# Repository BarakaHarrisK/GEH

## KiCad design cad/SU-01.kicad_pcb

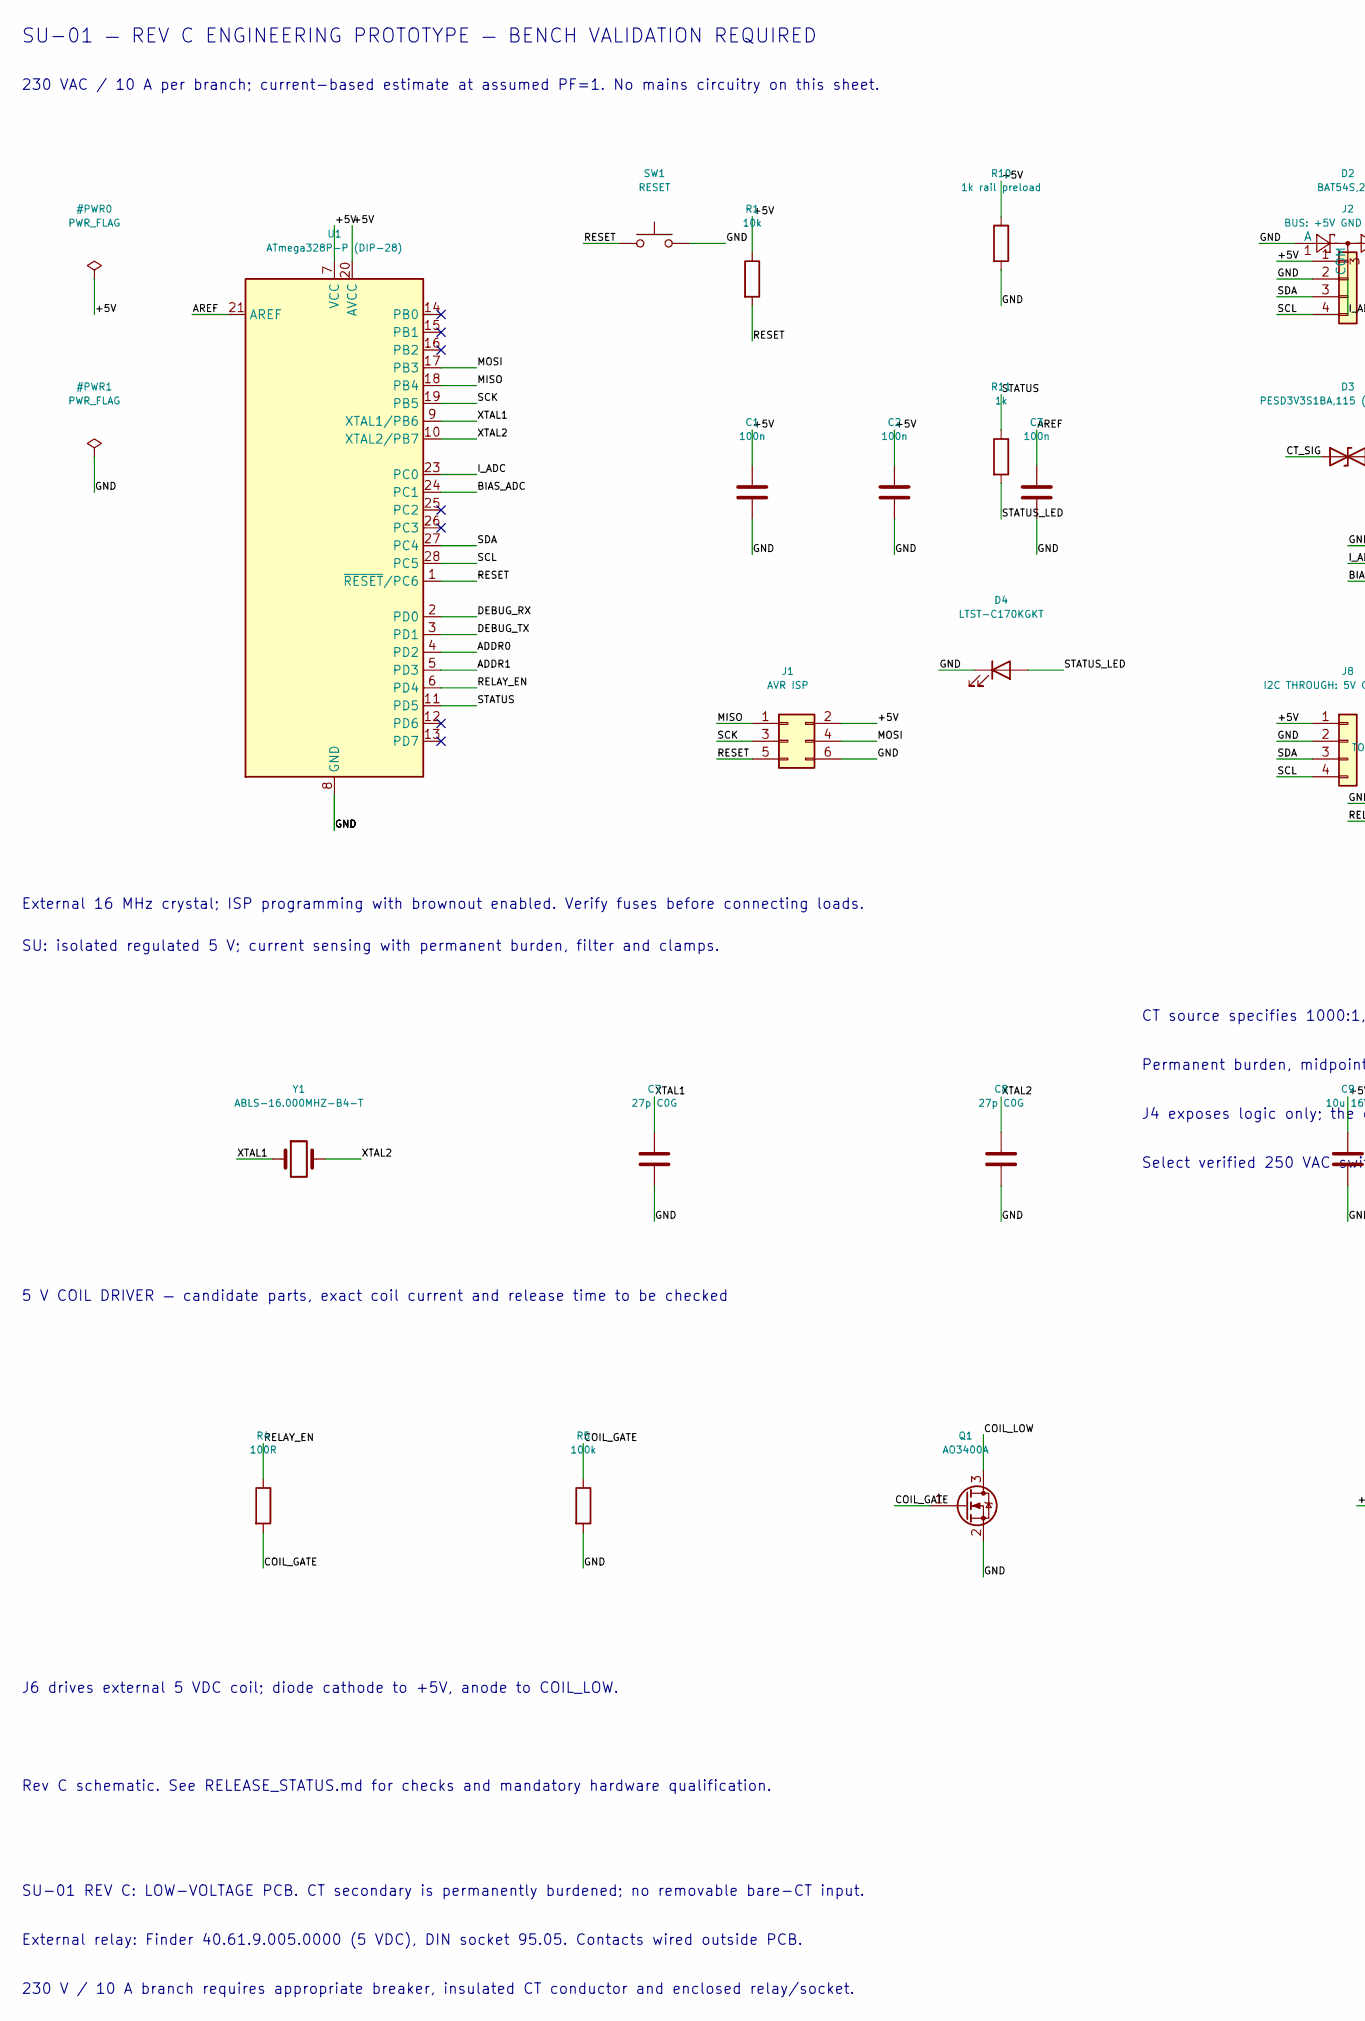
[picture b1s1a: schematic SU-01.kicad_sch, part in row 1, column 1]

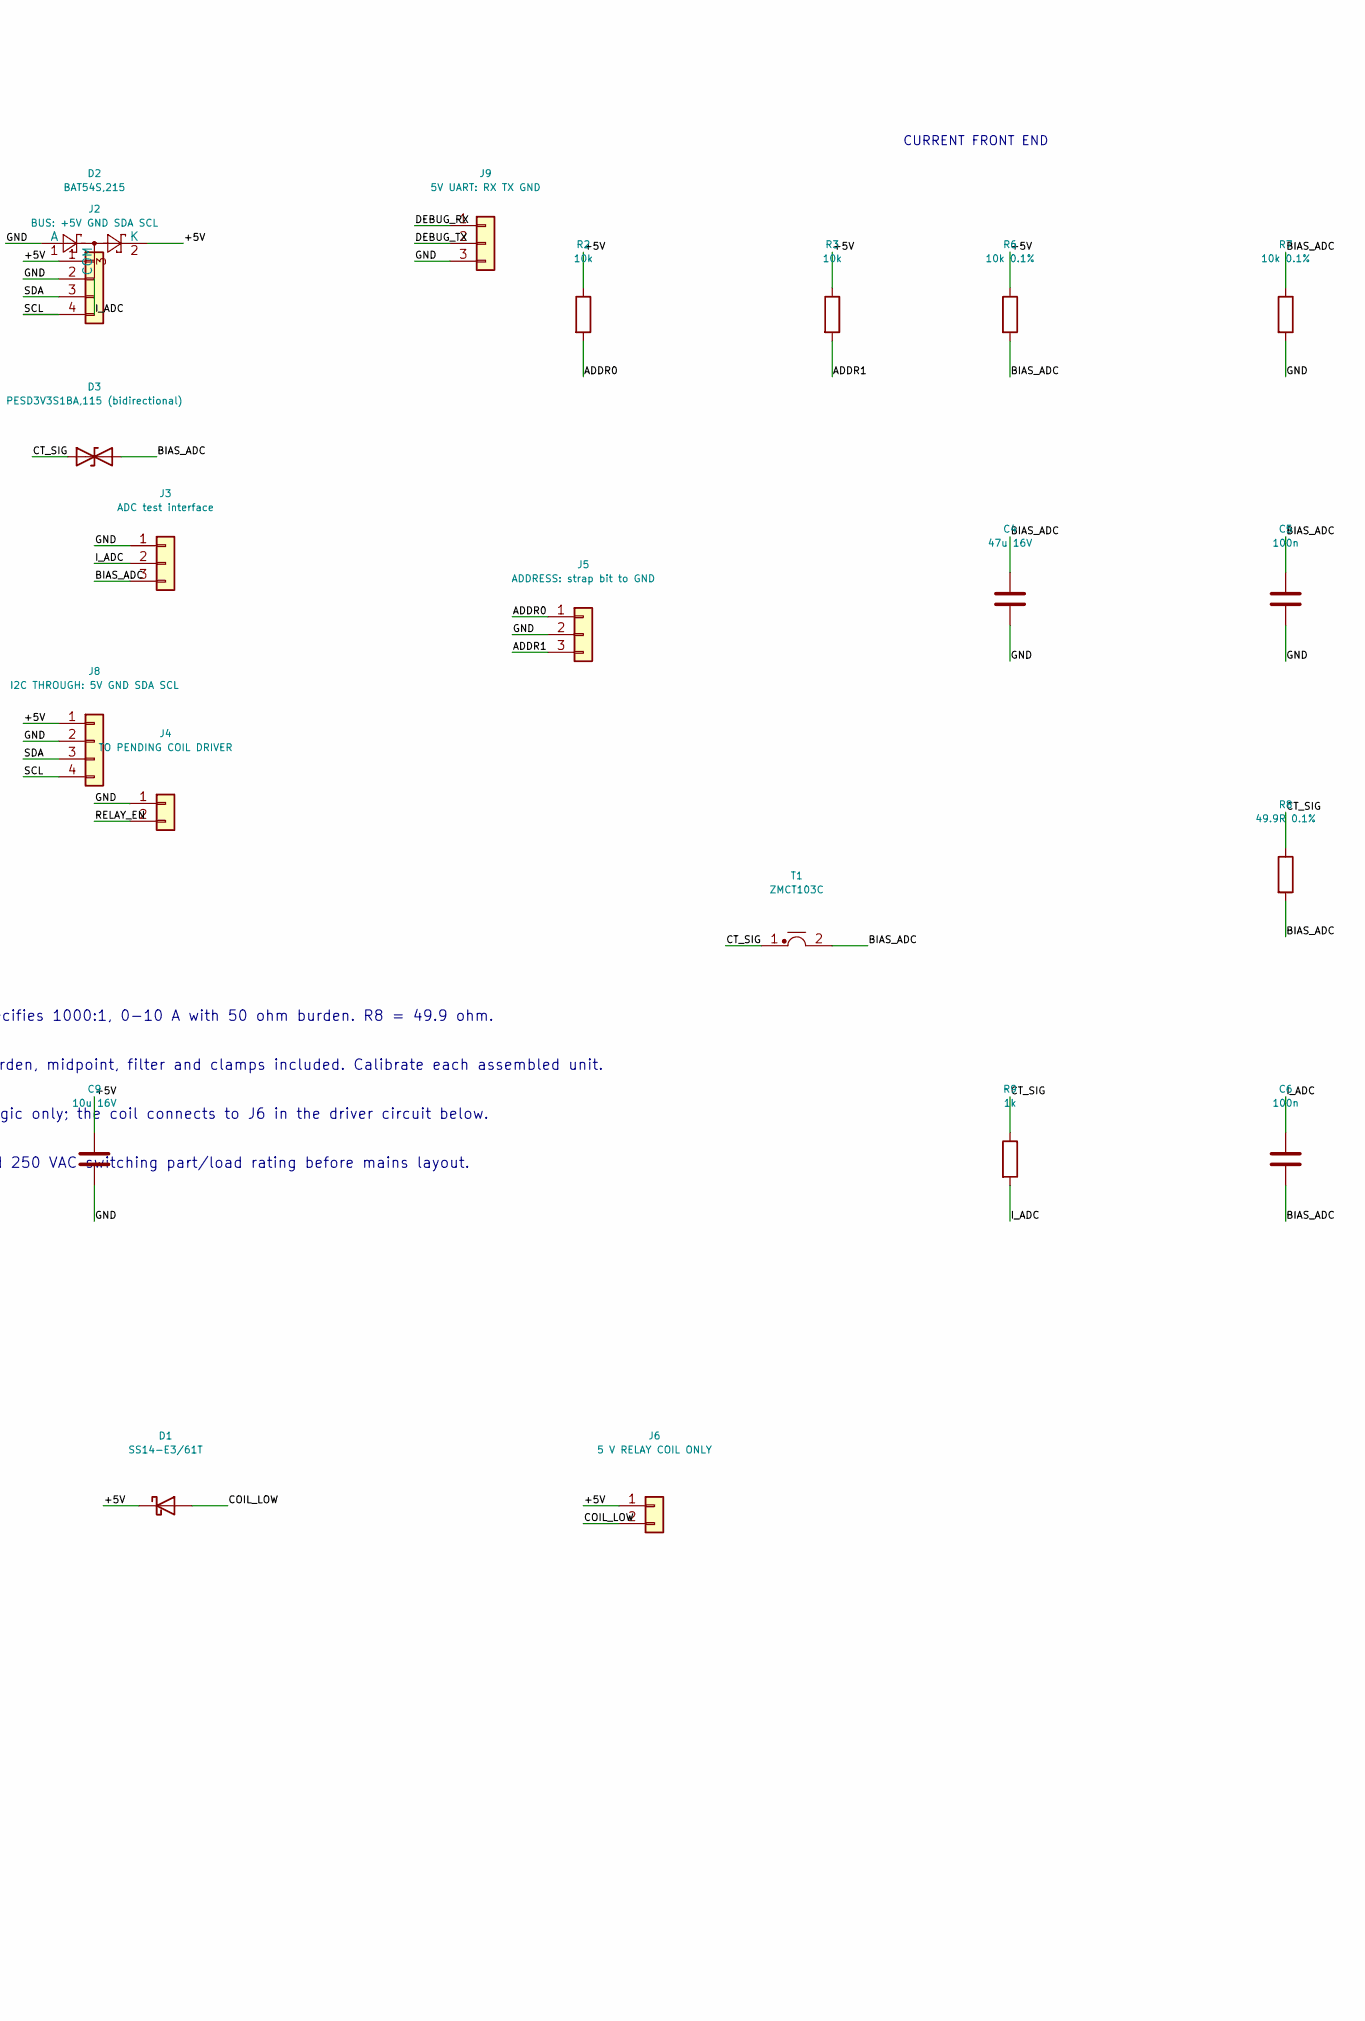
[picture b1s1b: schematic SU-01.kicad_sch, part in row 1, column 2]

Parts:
C1, C2, C3, C5, C6: 100n; C_0805_2012Metric
C4: 47u 16V; CP_Radial_D5.0mm_P2.00mm
C7, C8: 27p C0G; C_0805_2012Metric
C9: 10u 16V; C_1206_3216Metric
D1: SS14-E3/61T; D_SMA
D2: BAT54S,215; SOT-23
D3: PESD3V3S1BA,115 (bidirectional); D_SOD-323
D4: LTST-C170KGKT; LED_0805_2012Metric
J1: AVR ISP; IDC-Header_2x03_P2.54mm_Vertical
J2: BUS: +5V GND SDA SCL; JST_XH_B4B-XH-A_1x04_P2.50mm_Vertical
J3: ADC test interface; PinHeader_1x03_P2.54mm_Vertical
J4: TO PENDING COIL DRIVER; PinHeader_1x02_P2.54mm_Vertical
J5: ADDRESS: strap bit to GND; PinHeader_1x03_P2.54mm_Vertical
J6: 5 V RELAY COIL ONLY; TerminalBlock_Phoenix_MKDS-1,5-2-5.08_1x02_P5.08mm_Horizont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
J8: I2C THROUGH: 5V GND SDA SCL; JST_XH_B4B-XH-A_1x04_P2.50mm_Vertical
J9: 5V UART: RX TX GND; PinHeader_1x03_P2.54mm_Vertical
Q1: AO3400A; SOT-23
R1, R2, R3: 10k; R_0805_2012Metric
R4: 100R; R_0805_2012Metric
R5: 100k; R_0805_2012Metric
R6, R7: 10k 0.1%; R_0805_2012Metric
R8: 49.9R 0.1%; R_0805_2012Metric
R9, R11: 1k; R_0805_2012Metric
R10: 1k rail preload; R_0805_2012Metric
SW1: RESET; SW_PUSH_6mm
T1: ZMCT103C; Transformer_Zeming_ZMCT103C
U1: ATmega328P-P (DIP-28); DIP-28_W7.62mm
Y1: ABLS-16.000MHZ-B4-T; Crystal_HC49-4H_Vertical

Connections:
/ADDR0: J5.1, R2.2, U1.4 (PD2)
/ADDR1: J5.3, R3.2, U1.5 (PD3)
/AREF: C3.1, U1.21 (AREF)
/BIAS_ADC: C4.1, C5.1, C6.2, D3.2 (A2), J3.3, R6.2, R7.1, R8.2, T1.2, U1.24 (PC1)
/COIL_GATE: Q1.1 (G), R4.2, R5.1
/COIL_LOW: D1.2 (A), J6.2, Q1.3 (D)
/CT_SIG: D3.1 (A1), R8.1, R9.1, T1.1
/DEBUG_RX: J9.1, U1.2 (PD0)
/DEBUG_TX: J9.2, U1.3 (PD1)
/I_ADC: C6.1, D2.3 (COM), J3.2, R9.2, U1.23 (PC0)
/MISO: J1.1, U1.18 (PB4)
/MOSI: J1.4, U1.17 (PB3)
/RELAY_EN: J4.2, R4.1, U1.6 (PD4)
/RESET: J1.5, R1.2, SW1.1, U1.1 (~RESET/PC6)
/SCK: J1.3, U1.19 (PB5)
/SCL: J2.4, J8.4, U1.28 (PC5)
/SDA: J2.3, J8.3, U1.27 (PC4)
/STATUS: R11.1, U1.11 (PD5)
/STATUS_LED: D4.2 (A), R11.2
/XTAL1: C7.1, U1.9 (XTAL1/PB6), Y1.1
/XTAL2: C8.1, U1.10 (XTAL2/PB7), Y1.2

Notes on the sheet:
SU-01 — REV C ENGINEERING PROTOTYPE — BENCH VALIDATION REQUIRED
230 VAC / 10 A per branch; current-based estimate at assumed PF=1. No mains circuitry on this sheet.
External 16 MHz crystal; ISP programming with brownout enabled. Verify fuses before connecting loads.
SU: isolated regulated 5 V; current sensing with permanent burden, filter and clamps.
CT source specifies 1000:1, 0-10 A with 50 ohm burden. R8 = 49.9 ohm.
Permanent burden, midpoint, filter and clamps included. Calibrate each assembled unit.
J4 exposes logic only; the coil connects to J6 in the driver circuit below.
Select verified 250 VAC switching part/load rating before mains layout.
CURRENT FRONT END
5 V COIL DRIVER — candidate parts, exact coil current and release time to be checked
J6 drives external 5 VDC coil; diode cathode to +5V, anode to COIL_LOW.
SU-01 REV C: LOW-VOLTAGE PCB. CT secondary is permanently burdened; no removable bare-CT input.
External relay: Finder 40.61.9.005.0000 (5 VDC), DIN socket 95.05. Contacts wired outside PCB.
230 V / 10 A branch requires appropriate breaker, insulated CT conductor and enclosed relay/socket.
Rev C schematic. See RELEASE_STATUS.md for checks and mandatory hardware qualification.

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
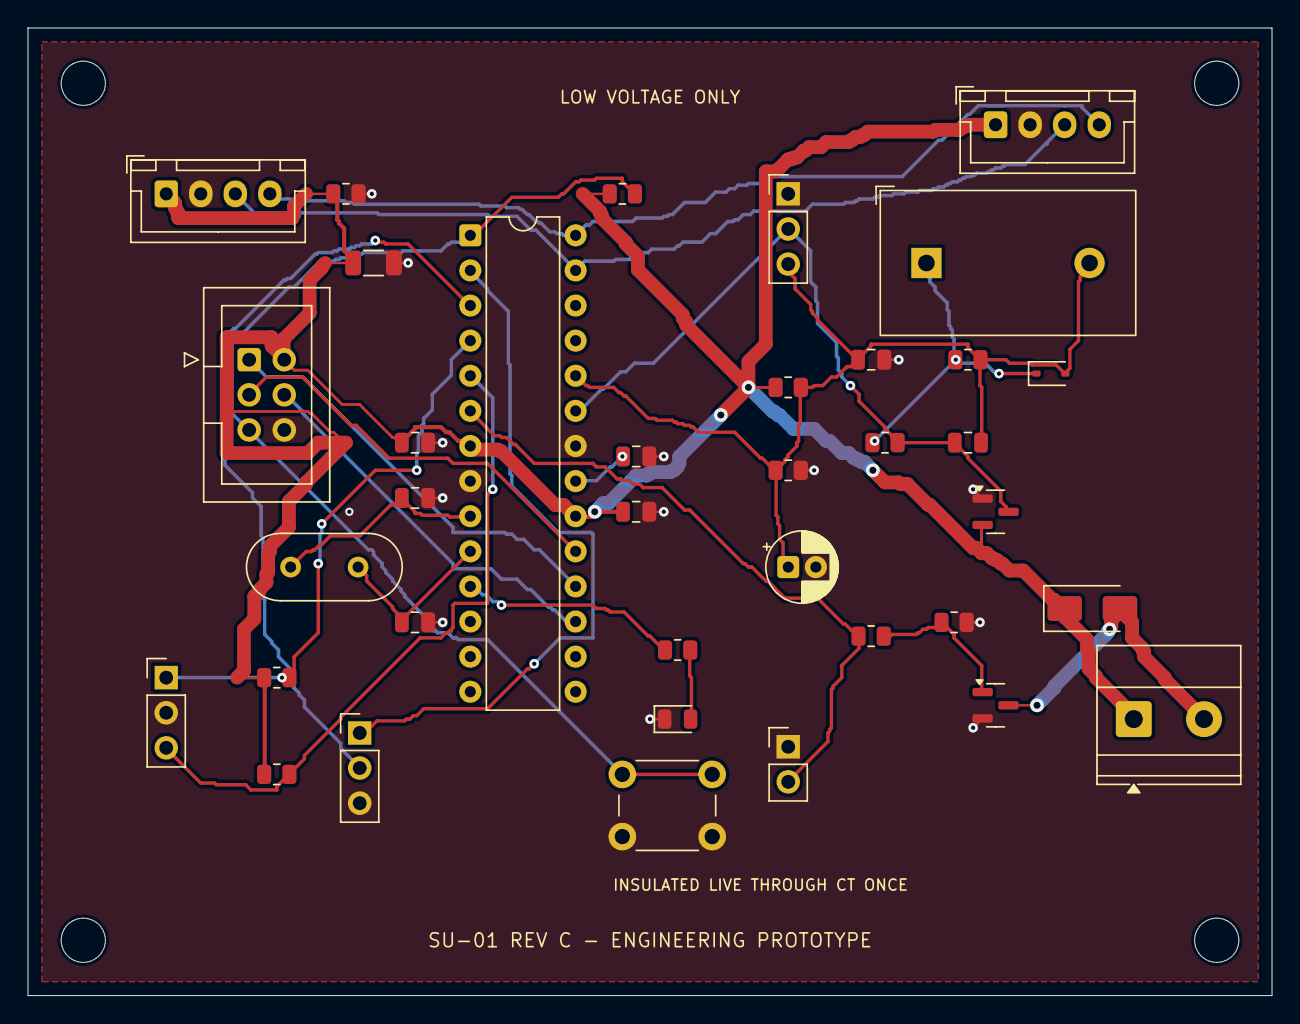
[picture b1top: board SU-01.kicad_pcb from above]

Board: 2 copper layers, 90.0 x 70.0 mm, 41 parts (0 on the bottom side), 23 nets.

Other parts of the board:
H1, H2, H3, H4: MountingHole_3.2mm_M3

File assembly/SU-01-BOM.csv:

Board,References,Qty per board,Qty for system,Value,Manufacturer part number,Footprint,Procurement requirements
SU-01,"C1,C2,C3,C5,C6",5,20,100n,,Capacitor_SMD:C_0805_2012Metric,100n; voltage >=stated or 25 V if unstated; X7R unless C0G specified; verify effective capacitance under DC bias; match listed case size.
SU-01,C4,1,4,47u 16V,,Capacitor_THT:CP_Radial_D5.0mm_P2.00mm,"47u 16V; radial, 5 mm diameter, 2.0 mm lead pitch; >=105 C, low ESR."
SU-01,"C7,C8",2,8,27p C0G,,Capacitor_SMD:C_0805_2012Metric,27p C0G; voltage >=stated or 25 V if unstated; X7R unless C0G specified; verify effective capacitance under DC bias; match listed case size.
SU-01,C9,1,4,10u 16V,,Capacitor_SMD:C_1206_3216Metric,10u 16V; voltage >=stated or 25 V if unstated; X7R unless C0G specified; verify effective capacitance under DC bias; match listed case size.
SU-01,D1,1,4,SS14-E3/61T,SS14-E3/61T,Diode_SMD:D_SMA,Use exact MPN and package; no unreviewed substitutions
SU-01,D2,1,4,"BAT54S,215","BAT54S,215",Package_TO_SOT_SMD:SOT-23,Use exact MPN and package; no unreviewed substitutions
SU-01,D3,1,4,"PESD3V3S1BA,115 (bidirectional)","PESD3V3S1BA,115",Diode_SMD:D_SOD-323,Use exact MPN and package; no unreviewed substitutions
SU-01,D4,1,4,LTST-C170KGKT,LTST-C170KGKT,LED_SMD:LED_0805_2012Metric,Use exact MPN and package; no unreviewed substitutions
SU-01,J1,1,4,AVR ISP,,Connector_IDC:IDC-Header_2x03_P2.54mm_Vertical,AVR ISP; standard 2.54 mm header matching listed footprint; pin numbers in connector schedule
SU-01,J2,1,4,BUS: +5V GND SDA SCL,B4B-XH-A(LF)(SN),Connector_JST:JST_XH_B4B-XH-A_1x04_P2.50mm_Vertical,JST XH 4-pin; mating XHP-4 with SXH-001T-P0.6 crimp contacts
SU-01,J3,1,4,ADC test interface,,Connector_PinHeader_2.54mm:PinHeader_1x03_P2.54mm_Vertical,ADC test interface; standard 2.54 mm header matching listed footprint; pin numbers in connector schedule
SU-01,J4,1,4,TO PENDING COIL DRIVER,,Connector_PinHeader_2.54mm:PinHeader_1x02_P2.54mm_Vertical,TO PENDING COIL DRIVER; standard 2.54 mm header matching listed footprint; pin numbers in connector schedule
SU-01,J5,1,4,ADDRESS: strap bit to GND,,Connector_PinHeader_2.54mm:PinHeader_1x03_P2.54mm_Vertical,ADDRESS: strap bit to GND; standard 2.54 mm header matching listed footprint; pin numbers in connector schedule
SU-01,J6,1,4,5 V RELAY COIL ONLY,Phoenix Contact 1715721,"TerminalBlock_Phoenix:TerminalBlock_Phoenix_MKDS-1,5-2-5.08_1x02_P5.08mm_Horizontal",MKDS 1.5/2-5.08 coil connector; verify exact terminal outline against selected drawing
SU-01,J8,1,4,I2C THROUGH: 5V GND SDA SCL,B4B-XH-A(LF)(SN),Connector_JST:JST_XH_B4B-XH-A_1x04_P2.50mm_Vertical,JST XH 4-pin; mating XHP-4 with SXH-001T-P0.6 crimp contacts
SU-01,J9,1,4,5V UART: RX TX GND,,Connector_PinHeader_2.54mm:PinHeader_1x03_P2.54mm_Vertical,5V UART: RX TX GND; standard 2.54 mm header matching listed footprint; pin numbers in connector schedule
SU-01,Q1,1,4,AO3400A,AO3400A,Package_TO_SOT_SMD:SOT-23,Use exact MPN and package; no unreviewed substitutions
SU-01,"R1,R2,R3",3,12,10k,,Resistor_SMD:R_0805_2012Metric,10k; 0805 >=0.125 W unless footprint is 2512 (>=1 W); stated 0.1% values require precision thin-film; other resistors 1%.
SU-01,R10,1,4,1k rail preload,,Resistor_SMD:R_0805_2012Metric,1k rail preload; 0805 >=0.125 W unless footprint is 2512 (>=1 W); stated 0.1% values require precision thin-film; other resistors 1%.
SU-01,R4,1,4,100R,,Resistor_SMD:R_0805_2012Metric,100R; 0805 >=0.125 W unless footprint is 2512 (>=1 W); stated 0.1% values require precision thin-film; other resistors 1%.
SU-01,R5,1,4,100k,,Resistor_SMD:R_0805_2012Metric,100k; 0805 >=0.125 W unless footprint is 2512 (>=1 W); stated 0.1% values require precision thin-film; other resistors 1%.
SU-01,"R6,R7",2,8,10k 0.1%,,Resistor_SMD:R_0805_2012Metric,10k 0.1%; 0805 >=0.125 W unless footprint is 2512 (>=1 W); stated 0.1% values require precision thin-film; other resistors 1%.
SU-01,R8,1,4,49.9R 0.1%,,Resistor_SMD:R_0805_2012Metric,49.9R 0.1%; 0805 >=0.125 W unless footprint is 2512 (>=1 W); stated 0.1% values require precision thin-film; other resistors 1%.
SU-01,"R9,R11",2,8,1k,,Resistor_SMD:R_0805_2012Metric,1k; 0805 >=0.125 W unless footprint is 2512 (>=1 W); stated 0.1% values require precision thin-film; other resistors 1%.
SU-01,SW1,1,4,RESET,,Button_Switch_THT:SW_PUSH_6mm,"6 x 6 mm through-hole normally-open tactile switch, pin layout matches footprint"
SU-01,T1,1,4,ZMCT103C,ZMCT103C,Transformer_THT:Transformer_Zeming_ZMCT103C,Use exact MPN and package; no unreviewed substitutions
SU-01,U1,1,4,ATmega328P-P (DIP-28),ATMEGA328P-PU,Package_DIP:DIP-28_W7.62mm,Use exact MPN and package; no unreviewed substitutions
SU-01,Y1,1,4,ABLS-16.000MHZ-B4-T,ABLS-16.000MHZ-B4-T,Crystal:Crystal_HC49-4H_Vertical,Use exact MPN and package; no unreviewed substitutions

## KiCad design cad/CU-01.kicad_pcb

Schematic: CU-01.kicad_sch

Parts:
BT1: 18650 3.7V 2600mAh cell 1; BatteryHolder_Keystone_1042_1x18650
BT2: 18650 3.7V 2600mAh cell 2; BatteryHolder_Keystone_1042_1x18650
C1, C2, C3, C6, C7, C8, C9, C15, C21, C22, C33, C38, C39, C42, C43: 100n; C_0805_2012Metric
C4, C5: 1u; C_0805_2012Metric
C10, C16: 10u 25V X7R; C_1210_3225Metric
C12, C17, C20, C30, C31, C32: 100n 25V; C_0805_2012Metric
C13, C14, C19: 22u 25V X7R; C_1210_3225Metric
C18: 3.3n; C_0805_2012Metric
C23: 47n 25V; C_0805_2012Metric
C24, C25: 1u 25V; C_0805_2012Metric
C26: 1u 10V; C_0805_2012Metric
C27, C28, C29: 10u 25V; C_1210_3225Metric
C34, C35: 100n 16V; C_0805_2012Metric
C36, C37: 100n 10V; C_0805_2012Metric
C40, C41: 27p C0G; C_0805_2012Metric
D2, D3: BAT46W-E3-08; D_SOD-123
D4: LTST-C170KGKT; LED_0805_2012Metric
D5: LTST-C170KRKT; LED_0805_2012Metric
D6: BZT52C12-E3-08; D_SOD-123
F1, F2: 0451003.MRL 3A 125V; Fuse_Littelfuse-NANO2-451_453
J1: AVR ISP; IDC-Header_2x03_P2.54mm_Vertical
J2: BUS: mains-only 5 V, GND, SDA, SCL; JST_XH_B4B-XH-A_1x04_P2.50mm_Vertical
J3: 4x4 passive keypad; PinHeader_1x08_P2.54mm_Vertical
J4: LCD1602 5V 20mA BACKLIGHT; PinHeader_1x16_P2.54mm_Vertical
J5: GSM INTERFACE TO PENDING CIRCUIT; PinHeader_1x04_P2.54mm_Vertical
J6: SIM800L HARNESS (not module footprint); JST_XH_B5B-XH-A_1x05_P2.50mm_Vertical
J7: ISOLATED 12 V INPUT; TerminalBlock_Phoenix_MKDS-3-2-5.08_1x02_P5.08mm_Horizontal
J9: CHARGE INHIBIT: short ISET to GND; PinHeader_1x02_P2.54mm_Vertical
J10: CELL TEMPERATURE SENSOR; JST_XH_B2B-XH-A_1x02_P2.50mm_Vertical
L2: XAL6030-222MEB 2.2uH; L_Coilcraft_XAL6030-XXX
L3: XAL6030-332MEB 3.3uH; L_Coilcraft_XAL6030-XXX
Q1: MMBT3904; SOT-23
Q2: MMBT3904 adapter detect; SOT-23
Q3, Q4, Q6, Q7: IRLR7843TRPBF; TO-252-2
Q5, Q11: IRFR5305TRPBF; TO-252-2
Q8, Q9, Q10: AO3400A; SOT-23
R1, R4, R17, R21, R36, R54: 10k; R_0805_2012Metric
R2, R3: 4.7k; R_0805_2012Metric
R5, R11, R14, R18, R19, R20, R49, R53, R56: 100k; R_0805_2012Metric
R6: 280R 0.1%; R_0805_2012Metric
R7: 121R 0.1%; R_0805_2012Metric
R9: 523k 0.1%; R_0805_2012Metric
R10, R45: 100k 0.1%; R_0805_2012Metric
R12: 165k 0.1%; R_0805_2012Metric
R13, R31: 10k 0.1%; R_0805_2012Metric
R15, R16: 4k7 provisional; R_0805_2012Metric
R22, R23: 4.02k; R_0805_2012Metric
R24, R50, R51: 1k; R_0805_2012Metric
R25, R27: 20m 1% 1W; R_2512_6332Metric
R26: 10R; R_0805_2012Metric
R28: 25.5k 0.1%; R_0805_2012Metric
R29: 2k 0.1%; R_0805_2012Metric
R30: 23.2k 0.1%; R_0805_2012Metric
R32: 249k 0.1%; R_0805_2012Metric
R33: 32.4k 0.1%; R_0805_2012Metric
R34: 5.23k 0.1%; R_0805_2012Metric
R35: 30.1k 0.1%; R_0805_2012Metric
R37, R38: 330R; R_0805_2012Metric
R39: 2k; R_0805_2012Metric
R40: 50m 1% 1W; R_2512_6332Metric
R41, R43, R52: 100R; R_0805_2012Metric
R42, R44: 62R 1% 1W; R_2512_6332Metric
R46, R48: 47k 0.1%; R_0805_2012Metric
R47: 200k 0.1%; R_0805_2012Metric
R55: 1.50M 0.1%; R_0805_2012Metric
RV1: 3296W-1-103LF 10k; Potentiometer_Bourns_3296W_Vertical
SW1: RESET; SW_PUSH_6mm
U1: ATmega328P-P (DIP-28); DIP-28_W7.62mm
U2: SN74LVC1T45DBVR TX; SOT-23-6
U3: SN74LVC1T45DBVR RX; SOT-23-6
U4: TLV75528PDBVR; SOT-23-5
U5: LT1764AET#PBF 3A LDO; LT1764A_TO2205_EnhancedPads
U6: TPS62130RGTR - 5 V; VQFN-16-1EP_3x3mm_P0.5mm_EP1.68x1.68mm
U7: TPS3700DDCR; SOT-23-6
U8: TCA9517ADGKR; VSSOP-8_3x3mm_P0.65mm
U9: BQ24133RGYR; Texas_RGY_R-PVQFN-N24_EP2.05x3.1mm
U10: HY2120-CB; SOT-23-6
U11, U12: HY2213-BB3A; SOT-23-6
U13: MCP23017-E/SP; DIP-28_W7.62mm
U14: FM24C64B-GTR; SOIC-8_3.9x4.9mm_P1.27mm
Y1: ABLS-16.000MHZ-B4-T; Crystal_HC49-4H_Vertical

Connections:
/+2V8: C5.1, C7.1, C9.1, U2.6 (VCCB), U3.6 (VCCB), U4.5 (OUT)
/+4V_GSM: C4.1, C13.1, C14.1, C15.1, J6.1, R6.1, U4.1 (IN), U4.3 (EN), U5.4 (OUT)
/+5V: C1.1, C2.1, C6.1, C8.1, C10.1, C12.1, C19.1, C21.1, C38.1, C39.1, J1.2, J4.2, L2.2, R1.1, R2.1, R3.1, R9.1, R11.1, R21.1, R52.1, R54.1, RV1.1, U1.7 (VCC), U1.20 (AVCC), U2.1 (VCCA), U2.5 (DIR), U3.1 (VCCA), U5.2 (IN), U6.14 (VOS), U8.1 (VCCA), U13.9 (VDD), U13.17 (A2), U14.8 (VDD)
/+5V_SERVICE: C22.1, J2.1, R15.1, R16.1, R17.1, U8.8 (VCCB)
/AC_COMMON: Q3.3 (S), Q4.3 (S), R23.2
/AC_DETECT_BASE: Q2.1 (B), R19.2, R20.1
/AC_GATE: Q3.1 (G), Q4.1 (G), R22.2
/AC_SENSE: C30.1, C32.1, Q4.2 (D), R25.1, U9.6 (ACP)
/ADAPTER_12V: F2.1, J7.1
/ADAPTER_FUSED: F2.2, Q11.2 (D)
/ADAPTER_PRESENT_N: Q2.3 (C), R21.2, U1.5 (PD3)
/ADAPTER_PROTECTED: D2.2 (A), D6.1 (K), Q3.2 (D), Q11.3 (S), R19.1, R32.1
/AREF: C3.1, U1.21 (AREF)
/BAL_DRAIN0: Q8.3 (D), R42.2
/BAL_DRAIN1: Q9.3 (D), R44.2
/BAL_GATE0: Q8.1 (G), U11.6 (OUT)
/BAL_GATE1: Q9.1 (G), U12.6 (OUT)
/BAT_GATE: Q5.1 (G), R24.2
/BUS_ENABLE: R17.2, R18.1, U8.5 (EN)
/CELL_POS: BT2.1 (+), F1.1, R37.1, R43.1, R44.1
/CHG_ACDRV: R22.1, U9.8 (ACDRV)
/CHG_ACSET: R30.2, R31.1, U9.17 (ACSET)
/CHG_AVCC_OR: D2.1 (K), D3.1 (K), R26.1
/CHG_BATDRV: R24.1, U9.19 (~BATDRV)
/CHG_BTST: C23.1, U9.21 (BTST)
/CHG_CMSRC: R23.1, U9.7 (CMSRC)
/CHG_ISET: J9.1, R28.2, R29.1, U9.13 (ISET)
/CHG_OVP: R32.2, R33.1, U9.18 (OVPSET)
/CHG_REGN: C24.1, U9.20 (REGN)
/CHG_STAT_N: R36.2, U1.14 (PB0), U9.9 (STAT)
/CHG_SW: C23.2, L3.1, U9.1 (SW), U9.24 (SW)
/CHG_TTC: C33.1, U9.11 (TTC)
/CHG_VREF: C26.1, R28.1, R30.1, R34.1, R36.1, U9.12 (VREF)
/CTRL_FB: R9.2, R10.1, U6.5 (FB)
/CTRL_PG: R11.2, U6.4 (PG)
/CTRL_RUN: R14.2, R55.1, U6.13 (EN), U7.1 (OUTA)
/CTRL_SS: C18.1, U6.9 (SS/TR)
/CTRL_SW: L2.1, U6.1 (SW), U6.2 (SW), U6.3 (SW)
/FAULT_LED: R51.1, U1.13 (PD7)
/GND: C1.2, C2.2, C3.2, C4.2, C5.2, C6.2, C7.2, C8.2, C9.2, C10.2, C12.2, C13.2, C14.2, C15.2, C16.2, C17.2, C18.2, C19.2, C20.2, C21.2, C22.2, C24.2, C25.2, C26.2, C27.2, C28.2, C29.2, C32.2, C33.2, C38.2, C39.2, C40.2, C41.2, C42.2, C43.2, D4.1 (K), D5.1 (K), J1.6, J2.2, J4.1, J4.5, J5.1, J6.2, J7.2, J9.2, J10.2, Q1.2 (E), Q2.2 (E), Q10.2 (S), R5.2, R7.2, R10.2, R13.2, R18.2, R20.2, R29.2, R31.2, R33.2, R35.2, R39.1, R40.2, R46.2, R48.2, R49.2, R53.2, R56.2, RV1.3, SW1.2, U1.8 (GND), U1.22 (GND), U2.2 (GND), U3.2 (GND), U3.5 (DIR), U4.2 (GND), U5.3 (GND), U6.6 (GND), U6.8 (DEF), U6.15 (GND), U6.16 (GND), U6.17 (GND), U7.2 (GND), U7.4 (INB-), U8.4 (GND), U9.22 (PGND), U9.23 (PGND), U9.25 (AGND), U13.10 (VSS), U13.15 (A0), U13.16 (A1), U14.1 (A0), U14.2 (A1), U14.3 (A2), U14.4 (VSS), U14.7 (WP)
/GSM_ENABLE: R49.1, U1.6 (PD4), U5.1 (~SHDN)
/GSM_FB: R6.2, R7.1, U5.5 (ADJ)
/GSM_RESET_CTL: J5.4, R4.1, U1.11 (PD5)
/GSM_RX_5V: J5.3, U1.2 (PD0), U3.3 (A)
/GSM_TX_5V: J5.2, U1.3 (PD1), U2.3 (A)
/IO_INT_N: R54.2, U1.4 (PD2), U13.19 (INTB)
/KEY_C1: J3.5, U13.5 (GPB4)
/KEY_C2: J3.6, U13.6 (GPB5)
/KEY_C3: J3.7, U13.7 (GPB6)
/KEY_C4: J3.8, U13.8 (GPB7)
/KEY_R1: J3.1, U13.1 (GPB0)
/KEY_R2: J3.2, U13.2 (GPB1)
/KEY_R3: J3.3, U13.3 (GPB2)
/KEY_R4: J3.4, U13.4 (GPB3)
/LCD_A: J4.15, R52.2
/LCD_BL_GATE: Q10.1 (G), R53.1, U13.27 (GPA6)
/LCD_D4: J4.11, U13.23 (GPA2)
/LCD_D5: J4.12, U13.24 (GPA3)
/LCD_D6: J4.13, U13.25 (GPA4)
/LCD_D7: J4.14, U13.26 (GPA5)
/LCD_E: J4.6, U13.22 (GPA1)
/LCD_K: J4.16, Q10.3 (D)
/LCD_RS: J4.4, U13.21 (GPA0)
/LCD_VO: J4.3, RV1.2
/LED_GREEN: D4.2 (A), R50.2
/LED_RED: D5.2 (A), R51.2
/MISO: J1.1, U1.18 (PB4)
/MOSI: J1.4, U1.17 (PB3)
/PACK_ADC: C42.1, R45.2, R46.1, U1.23 (PC0)
/PACK_NTC: J10.1, R34.2, R35.1, U9.10 (TS)
/PACK_PROTECTED: C28.1, C29.1, C31.2, D3.2 (A), F1.2, Q5.2 (D), R27.2, R45.1, U9.15 (SRN)
/PCM_CS: R39.2, U10.3 (CS)
/PCM_DRAIN: Q6.2 (D), Q7.2 (D)
/PCM_OC: Q7.1 (G), U10.2 (OC)
/PCM_OD: Q6.1 (G), U10.1 (OD)
/PCM_SOURCE: Q7.3 (S), R40.1
/PCM_VC: C34.2, C35.1, R38.2, U10.4 (VC)
/RESET: J1.5, R1.2, SW1.1, U1.1 (~RESET/PC6), U13.18 (~RESET)
/RESET_BASE: Q1.1 (B), R4.2, R5.1
/REV_GATE: D6.2 (A), Q11.1 (G), R56.1
/SCK: J1.3, U1.19 (PB5)
/SCL: R3.2, U1.28 (PC5), U8.2 (SCLA), U13.12 (SCK), U14.6 (SCL)
/SCL_BUS: J2.4, R16.2, U8.7 (SCLB)
/SDA: R2.2, U1.27 (PC4), U8.3 (SDAA), U13.13 (SDA), U14.5 (SDA)
/SDA_BUS: J2.3, R15.2, U8.6 (SDAB)
/SIM_RST: J6.5, Q1.3 (C)
/SIM_RXD: J6.3, U2.4 (B)
/SIM_TXD: J6.4, U3.4 (B)
/STATUS_LED: R50.1, U1.12 (PD6)
/SYS_ADC: C43.1, R47.2, R48.1, U1.24 (PC1)
/SYS_RAW: C16.1, C17.1, C20.1, C27.1, C30.2, Q5.3 (S), R12.1, R14.1, R25.2, R47.1, U6.7 (FSW), U6.10 (VIN), U6.11 (VIN), U6.12 (VIN), U7.5 (VDD), U9.2 (PVCC), U9.3 (PVCC), U9.5 (ACN)
/SYS_UV: R12.2, R13.1, R55.2, U7.3 (INA+)
/XTAL1: C40.1, U1.9 (XTAL1/PB6), Y1.1
/XTAL2: C41.1, U1.10 (XTAL2/PB7), Y1.2

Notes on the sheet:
CU-01 — REV C ENGINEERING PROTOTYPE — BENCH VALIDATION REQUIRED
230 VAC / 10 A per branch; current-based estimate at assumed PF=1. No mains circuitry on this sheet.
External 16 MHz crystal; ISP programming with brownout enabled. Verify fuses before connecting loads.
CU: isolated 12 V input + protected 2S backup; service 5 V separate.
J5 is a logic test header; translated module signals are on J6.
GSM supply / translation below; J6 harness to SIM800L. FRAM and IO expander included.
J4 is a full 16-pin LCD interface; contrast and limited-current backlight included.
LCD/keypad use U13 I2C expander; ISP pins are dedicated.
GSM UART TRANSLATION — 5 V A-side / 2.8 V B-side
Verify module pin labels and reset pull-up before connecting.
2.8 V follows GSM 4 V supply; avoid UART drive in module soft-off.
GSM 4.01 V / 3 A LOW-NOISE LDO FROM BACKED 5 V
VOUT = 1.21 * (1 + 280/121) ~= 4.01 V. TO-220 tab is GND.
Regulator input is the 5 V buck. Qualify heat sink and 2 A radio bursts at worst ambient.
Minimum output capacitance 10 uF; retain module-local bulk capacitor and short power harness.
No fabrication release: verify exact MPNs/footprints, protection, mechanics and ERC.
Rev C schematic. See RELEASE_STATUS.md for checks and mandatory hardware qualification.
2S 18650 BACKUP — CANDIDATE CIRCUIT / MODULE INTERFACES
2S1P: 7.4 V nominal, 8.4 V full. 2600 mAh / 19.24 Wh nominal. Charge current 0.60 A.
CELL_NEG must NOT be shorted to GND (P-); no raw-cell load path.
5 V CONTROLLER BUCK + LOW-VOLTAGE CUTOFF
External hysteresis: SYS starts ~7.04 V / stops ~6.30 V. Verify tolerances and burst recovery.
No runtime guarantee: usable Wh, GSM activity, LCD load, losses and cutoff need measurement.
BACKUP BUS ISOLATION — service boards remain mains powered
J2 pin 1 is now mains-only +5V_SERVICE, not battery-backed +5V. Supply it externally.
U8 isolates I2C when the service supply is off; validate all power-up/down combinations.
PB6 / DIP pin 9: low = adapter present; high = adapter lost. No crystal on this pin.
Firmware should save state, report outage and reduce LCD load; hard cutoff is independent.
INTEGRATED CHARGER / POWER PATH — BQ24133, hardware-selected 2S, 0.60 A target
CELL pin intentionally NC = 2S / 8.4 V. 100 nF TTC gives ~9.33 h fast-charge timer. NTC = Semitec 103AT-2 (on cells).
OVP nominal 13.90 V; adapter-valid lower threshold 4.34 V. ACSET = 2.50 A input limit. Verify Kelvin sense and thermal layout.
INTEGRATED CELL PROTECTION AND BALANCING
Per-cell HY2213 balancing begins near 4.2 V; 62 ohm bleeds approximately 68 mA / 0.285 W.
BMS OC/OD thresholds are independent of charger. Pack fuse and 50 milliohm shunt remain mandatory.
CONTROLLER I/O / CLOCK / NONVOLATILE RECORDS
I2C: MCP23017=0x24, FM24C64B=0x50; service units=0x20..0x23.
16 MHz crystal: CL=18pF; 27p capacitors assume ~4.5pF stray. Keep oscillator loop short.
LCD pin 1=GND, 2=5V, 3=VO, 4=RS, 5=GND, 6=E, 11..14=D4..D7, 15=A,16=K.
ISP lines are dedicated. Disable GSM rail via PD4 before module power-down to avoid UART phantom supply.

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
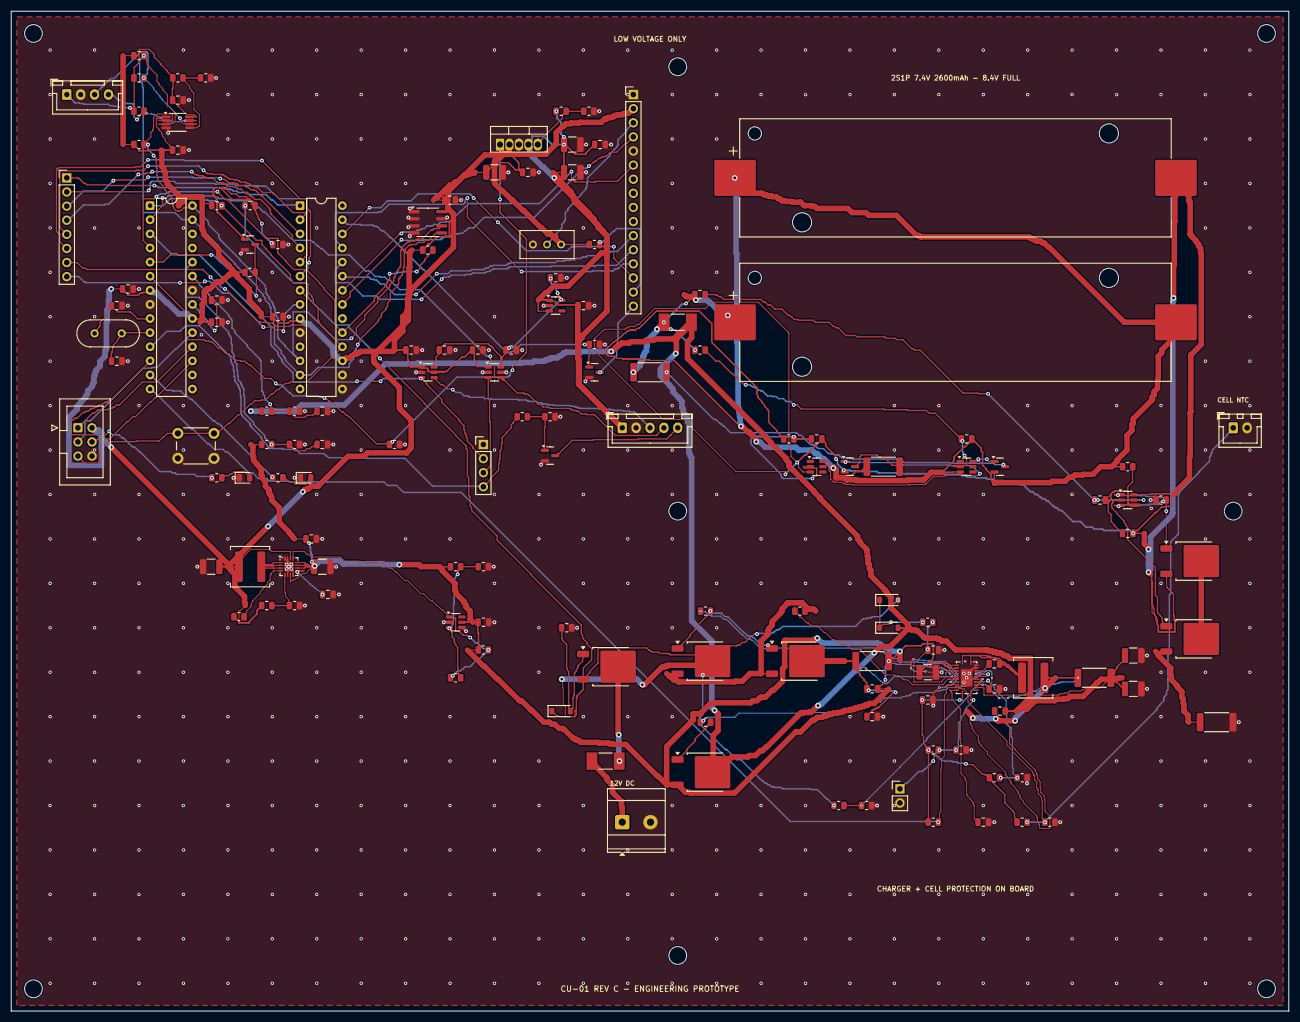
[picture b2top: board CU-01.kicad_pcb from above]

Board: 2 copper layers, 230.0 x 180.0 mm, 153 parts (0 on the bottom side), 101 nets.

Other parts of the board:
H1, H2, H3, H4, H5, H6, H7, H8: MountingHole_3.2mm_M3

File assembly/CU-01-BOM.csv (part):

Board,References,Qty per board,Qty for system,Value,Manufacturer part number,Footprint,Procurement requirements
CU-01,BT1,1,1,18650 3.7V 2600mAh cell 1,Keystone 1042,Battery:BatteryHolder_Keystone_1042_1x18650,Holder only; cells separately listed. Check polarity and cell dimensions.
CU-01,BT2,1,1,18650 3.7V 2600mAh cell 2,Keystone 1042,Battery:BatteryHolder_Keystone_1042_1x18650,Holder only; cells separately listed. Check polarity and cell dimensions.
CU-01,"C1,C2,C3,C6,C7,C8,C9,C15,C21,C22,C33,C38,C39,C42,C43",15,15,100n,,Capacitor_SMD:C_0805_2012Metric,100n; voltage >=stated or 25 V if unstated; X7R unless C0G specified; verify effective capacitance under DC bias; match listed case size.
CU-01,"C10,C16",2,2,10u 25V X7R,,Capacitor_SMD:C_1210_3225Metric,10u 25V X7R; voltage >=stated or 25 V if unstated; X7R unless C0G specified; verify effective capacitance under DC bias; match listed case size.
CU-01,"C12,C17,C20,C30,C31,C32",6,6,100n 25V,,Capacitor_SMD:C_0805_2012Metric,100n 25V; voltage >=stated or 25 V if unstated; X7R unless C0G specified; verify effective capacitance under DC bias; match listed case size.
CU-01,"C13,C14,C19",3,3,22u 25V X7R,,Capacitor_SMD:C_1210_3225Metric,22u 25V X7R; voltage >=stated or 25 V if unstated; X7R unless C0G specified; verify effective capacitance under DC bias; match listed case size.
CU-01,C18,1,1,3.3n,,Capacitor_SMD:C_0805_2012Metric,3.3n; voltage >=stated or 25 V if unstated; X7R unless C0G specified; verify effective capacitance under DC bias; match listed case size.
CU-01,C23,1,1,47n 25V,,Capacitor_SMD:C_0805_2012Metric,47n 25V; voltage >=stated or 25 V if unstated; X7R unless C0G specified; verify effective capacitance under DC bias; match listed case size.
CU-01,"C24,C25",2,2,1u 25V,,Capacitor_SMD:C_0805_2012Metric,1u 25V; voltage >=stated or 25 V if unstated; X7R unless C0G specified; verify effective capacitance under DC bias; match listed case size.
CU-01,C26,1,1,1u 10V,,Capacitor_SMD:C_0805_2012Metric,1u 10V; voltage >=stated or 25 V if unstated; X7R unless C0G specified; verify effective capacitance under DC bias; match listed case size.
CU-01,"C27,C28,C29",3,3,10u 25V,,Capacitor_SMD:C_1210_3225Metric,10u 25V; voltage >=stated or 25 V if unstated; X7R unless C0G specified; verify effective capacitance under DC bias; match listed case size.
CU-01,"C34,C35",2,2,100n 16V,,Capacitor_SMD:C_0805_2012Metric,100n 16V; voltage >=stated or 25 V if unstated; X7R unless C0G specified; verify effective capacitance under DC bias; match listed case size.
CU-01,"C36,C37",2,2,100n 10V,,Capacitor_SMD:C_0805_2012Metric,100n 10V; voltage >=stated or 25 V if unstated; X7R unless C0G specified; verify effective capacitance under DC bias; match listed case size.
CU-01,"C4,C5",2,2,1u,,Capacitor_SMD:C_0805_2012Metric,1u; voltage >=stated or 25 V if unstated; X7R unless C0G specified; verify effective capacitance under DC bias; match listed case size.
CU-01,"C40,C41",2,2,27p C0G,,Capacitor_SMD:C_0805_2012Metric,27p C0G; voltage >=stated or 25 V if unstated; X7R unless C0G specified; verify effective capacitance under DC bias; match listed case size.
CU-01,"D2,D3",2,2,BAT46W-E3-08,BAT46W-E3-08,Diode_SMD:D_SOD-123,Use exact MPN and package; no unreviewed substitutions
CU-01,D4,1,1,LTST-C170KGKT,LTST-C170KGKT,LED_SMD:LED_0805_2012Metric,Use exact MPN and package; no unreviewed substitutions
CU-01,D5,1,1,LTST-C170KRKT,LTST-C170KRKT,LED_SMD:LED_0805_2012Metric,Use exact MPN and package; no unreviewed substitutions
CU-01,D6,1,1,BZT52C12-E3-08,BZT52C12-E3-08,Diode_SMD:D_SOD-123,Use exact MPN and package; no unreviewed substitutions
CU-01,"F1,F2",2,2,0451003.MRL 3A 125V,0451003.MRL,Fuse:Fuse_Littelfuse-NANO2-451_453,Use exact MPN and package; no unreviewed substitutions
CU-01,J1,1,1,AVR ISP,,Connector_IDC:IDC-Header_2x03_P2.54mm_Vertical,AVR ISP; standard 2.54 mm header matching listed footprint; pin numbers in connector schedule
CU-01,J10,1,1,CELL TEMPERATURE SENSOR,B2B-XH-A(LF)(SN),Connector_JST:JST_XH_B2B-XH-A_1x02_P2.50mm_Vertical,JST XH 2-pin; mating XHP-2 with SXH-001T-P0.6 crimp contacts
CU-01,J2,1,1,"BUS: mains-only 5 V, GND, SDA, SCL",B4B-XH-A(LF)(SN),Connector_JST:JST_XH_B4B-XH-A_1x04_P2.50mm_Vertical,JST XH 4-pin; mating XHP-4 with SXH-001T-P0.6 crimp contacts
CU-01,J3,1,1,4x4 passive keypad,,Connector_PinHeader_2.54mm:PinHeader_1x08_P2.54mm_Vertical,4x4 passive keypad; standard 2.54 mm header matching listed footprint; pin numbers in connector schedule
CU-01,J4,1,1,LCD1602 5V 20mA BACKLIGHT,,Connector_PinHeader_2.54mm:PinHeader_1x16_P2.54mm_Vertical,LCD1602 5V 20mA BACKLIGHT; standard 2.54 mm header matching listed footprint; pin numbers in connector schedule
CU-01,J5,1,1,GSM INTERFACE TO PENDING CIRCUIT,,Connector_PinHeader_2.54mm:PinHeader_1x04_P2.54mm_Vertical,GSM INTERFACE TO PENDING CIRCUIT; standard 2.54 mm header matching listed footprint; pin numbers in connector schedule
CU-01,J6,1,1,SIM800L HARNESS (not module footprint),B5B-XH-A(LF)(SN),Connector_JST:JST_XH_B5B-XH-A_1x05_P2.50mm_Vertical,JST XH 5-pin; mating XHP-5 with SXH-001T-P0.6 crimp contacts
CU-01,J7,1,1,ISOLATED 12 V INPUT,Phoenix Contact 1711725,TerminalBlock_Phoenix:TerminalBlock_Phoenix_MKDS-3-2-5.08_1x02_P5.08mm_Horizontal,MKDS 3/2-5.08 input terminal; 12 V DC only
CU-01,J9,1,1,CHARGE INHIBIT: short ISET to GND,,Connector_PinHeader_2.54mm:PinHeader_1x02_P2.54mm_Vertical,CHARGE INHIBIT: short ISET to GND; standard 2.54 mm header matching listed footprint; pin numbers in connector schedule
CU-01,L2,1,1,XAL6030-222MEB 2.2uH,XAL6030-222MEB,Inductor_SMD:L_Coilcraft_XAL6030-XXX,Use exact MPN and package; no unreviewed substitutions
CU-01,L3,1,1,XAL6030-332MEB 3.3uH,XAL6030-332MEB,Inductor_SMD:L_Coilcraft_XAL6030-XXX,Use exact MPN and package; no unreviewed substitutions
CU-01,Q1,1,1,MMBT3904,MMBT3904LT1G,Package_TO_SOT_SMD:SOT-23,Use exact MPN and package; no unreviewed substitutions
CU-01,"Q11,Q5",2,2,IRFR5305TRPBF,IRFR5305TRPBF,Package_TO_SOT_SMD:TO-252-2,Use exact MPN and package; no unreviewed substitutions
CU-01,Q2,1,1,MMBT3904 adapter detect,MMBT3904LT1G,Package_TO_SOT_SMD:SOT-23,Use exact MPN and package; no unreviewed substitutions
CU-01,"Q3,Q4,Q6,Q7",4,4,IRLR7843TRPBF,IRLR7843TRPBF,Package_TO_SOT_SMD:TO-252-2,Use exact MPN and package; no unreviewed substitutions
CU-01,"Q8,Q9,Q10",3,3,AO3400A,AO3400A,Package_TO_SOT_SMD:SOT-23,Use exact MPN and package; no unreviewed substitutions
CU-01,"R1,R4,R17,R21,R36,R54",6,6,10k,,Resistor_SMD:R_0805_2012Metric,10k; 0805 >=0.125 W unless footprint is 2512 (>=1 W); stated 0.1% values require precision thin-film; other resistors 1%.
CU-01,"R10,R45",2,2,100k 0.1%,,Resistor_SMD:R_0805_2012Metric,100k 0.1%; 0805 >=0.125 W unless footprint is 2512 (>=1 W); stated 0.1% values require precision thin-film; other resistors 1%.
CU-01,R12,1,1,165k 0.1%,,Resistor_SMD:R_0805_2012Metric,165k 0.1%; 0805 >=0.125 W unless footprint is 2512 (>=1 W); stated 0.1% values require precision thin-film; other resistors 1%.
CU-01,"R13,R31",2,2,10k 0.1%,,Resistor_SMD:R_0805_2012Metric,10k 0.1%; 0805 >=0.125 W unless footprint is 2512 (>=1 W); stated 0.1% values require precision thin-film; other resistors 1%.
CU-01,"R15,R16",2,2,4k7 provisional,,Resistor_SMD:R_0805_2012Metric,4k7 provisional; 0805 >=0.125 W unless footprint is 2512 (>=1 W); stated 0.1% values require precision thin-film; other resistors 1%.
CU-01,"R2,R3",2,2,4.7k,,Resistor_SMD:R_0805_2012Metric,4.7k; 0805 >=0.125 W unless footprint is 2512 (>=1 W); stated 0.1% values require precision thin-film; other resistors 1%.
CU-01,"R22,R23",2,2,4.02k,,Resistor_SMD:R_0805_2012Metric,4.02k; 0805 >=0.125 W unless footprint is 2512 (>=1 W); stated 0.1% values require precision thin-film; other resistors 1%.
CU-01,"R24,R50,R51",3,3,1k,,Resistor_SMD:R_0805_2012Metric,1k; 0805 >=0.125 W unless footprint is 2512 (>=1 W); stated 0.1% values require precision thin-film; other resistors 1%.
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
